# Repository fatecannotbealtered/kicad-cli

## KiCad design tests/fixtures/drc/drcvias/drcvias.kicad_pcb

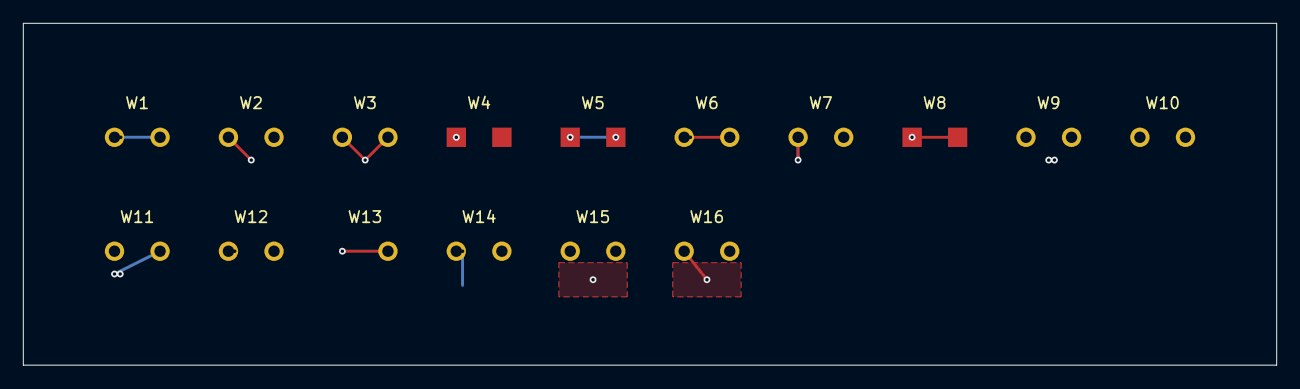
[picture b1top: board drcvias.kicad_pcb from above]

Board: 4 copper layers, 110.0 x 30.0 mm, 16 parts (0 on the bottom side), 16 nets.

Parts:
W1: W1
W2: W2
W3: W3
W4: W4
W5: W5
W6: W6
W7: W7
W8: W8
W9: W9
W10: W10
W11: W11
W12: W12
W13: W13
W14: W14
W15: W15
W16: W16

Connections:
W1: W1.1, W1.2
W2: W2.1, W2.2
W3: W3.1, W3.2
W4: W4.1, W4.2
W5: W5.1, W5.2
W6: W6.1, W6.2
W7: W7.1, W7.2
W8: W8.1, W8.2
W9: W9.1, W9.2
W10: W10.1, W10.2
W11: W11.1, W11.2
W12: W12.1, W12.2
W13: W13.1, W13.2
W14: W14.1, W14.2
W15: W15.1, W15.2
W16: W16.1, W16.2
